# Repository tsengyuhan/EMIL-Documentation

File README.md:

# EMIL-Documentation
The documentation of developing hardware design and wearable solutions.

test

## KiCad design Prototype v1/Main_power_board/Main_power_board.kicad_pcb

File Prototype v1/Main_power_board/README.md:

# Note: Main Power Board

### Features

- Input voltage: 6.2v - 20v (1.2v Maximum Dropout Voltage at 800 mA)
- Regulating the input voltage to 5v. 
- A main switch to turn on/off the entire system manually. 
- I2C connection to the master board. 
- An eneble pin to turn on/off the 

### Difference with the previous version

The trace width and via size are reduced because the manufacturer can produce PCBs with the machine and get more detailed and accurate results.

- Ordinary trace width: 0.4mm
- Via diameter: 0.5mm
- Via hole: 0.3mm
- To decrease the signal interference, I tried to separate the traces based on different signal transmissions (e.g. PWM, I2C, analog reading). 

### Pinout

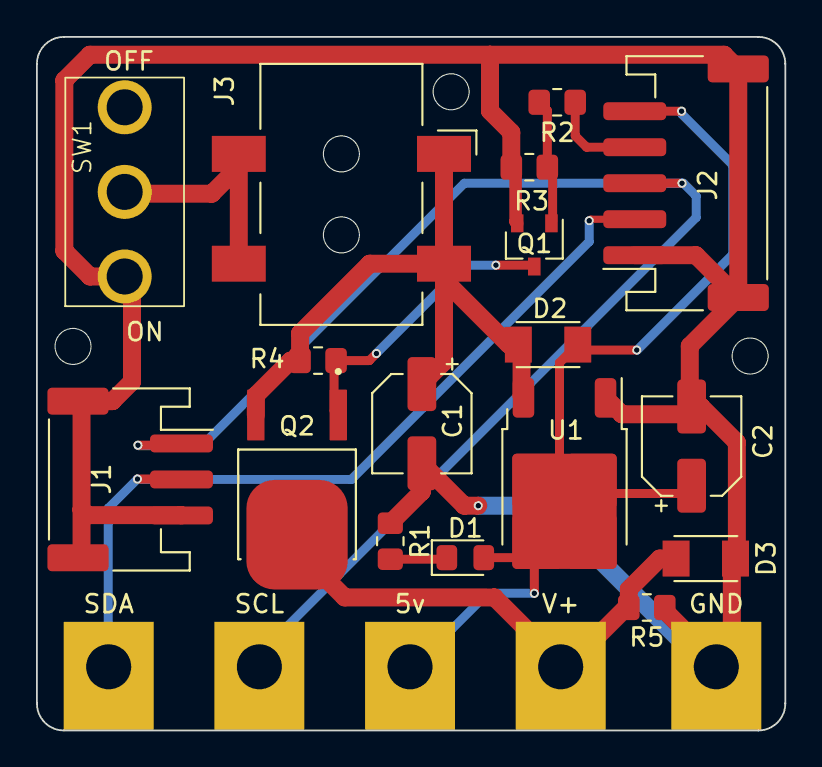
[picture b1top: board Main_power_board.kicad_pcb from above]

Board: 2 copper layers, 41.6 x 38.5 mm, 22 parts (0 on the bottom side), 11 nets.

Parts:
5v: MountingHole_Pad; MountingHole_2.5mm_Pad
C1, C2: 10uF; CP_Elec_5x5.4
D1: LED; LED_0805_2012Metric_Pad1.15x1.40mm_HandSolder
D2, D3: DIODE SCHOT 100V 1A MINISMA; SOD-123T
GND: MountingHole_Pad; MountingHole_2.5mm_Pad
J1: CONN HEADER SMD R/A 3POS 2MM; JST_PH_S3B-PH-SM4-TB_1x03-1MP_P2.00mm_Horizontal
J2: CONN HEADER SMD R/A 5POS 2MM; JST_PH_S5B-PH-SM4-TB_1x05-1MP_P2.00mm_Horizontal
J3: CONN PWR JACK 2X5.5MM; CUIDevices_PJ-002AH-SMT-TR_PWRJack_2x5.5mm
Q1: MOSFET N-CH 30V 1.7A SUPERSOT3; SOT-23-3
Q2: MOSFET P-CH 30V 25A DPAK; TO229P990X238-3N
R1: 499; R_0805_2012Metric_Pad1.20x1.40mm_HandSolder
R2, R3, R4: 10K; R_0805_2012Metric_Pad1.20x1.40mm_HandSolder
R5: 1K; R_0805_2012Metric_Pad1.20x1.40mm_HandSolder
SCL: MountingHole_Pad; MountingHole_2.5mm_Pad
SDA: MountingHole_Pad; MountingHole_2.5mm_Pad
SW1: SWITCH SLIDE SPDT 5A 120VAC; SW_SPDTx03_Slide
U1: IC REG LINEAR 5V 1A DPAK; TO-252-2
V+: MountingHole_Pad; MountingHole_2.5mm_Pad

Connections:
Enable: J2.4, R2.1
unnamed: D1.1 (K), R1.2
unnamed: Q1.3 (D), Q2.1 (G), R4.2
unnamed: Q1.1 (G), R2.2, R3.2
unnamed: J3.2, J3.3, SW1.2 (B)
OUTPUT_PWR: D3.1 (K), Q2.2 (D), R5.2, V+.1
PWR_5V: 5v.1, C2.1, D1.2 (A), D2.2 (A), J2.5, U1.2 (VO)
PWR_12V: C1.1, D2.1 (K), J3.1, Q2.3 (S), R4.1, U1.3 (VI)
PWR_GND: C1.2, C2.2, D3.2 (A), GND.1, J1.3, J2.1, Q1.2 (S), R1.1, R3.1, R5.1, SW1.1 (A), U1.1 (GND)
SCL: J1.1, J2.3, SCL.1
SDA: J1.2, J2.2, SDA.1

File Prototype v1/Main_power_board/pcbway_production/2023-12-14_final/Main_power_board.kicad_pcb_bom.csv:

designator,quantity,value,pack,mpn,mount_type
"C1, C2",2,10uF,CP_Elec_5x5.4,8.65081E+11,smt
D1,1,LED,LED_0805_2012Metric_Pad1.15x1.40mm_HandSolder,LTST-C171GKT,smt
"D2, D3",2,DIODE SCHOT 100V 1A MINISMA,SOD-123T,CDBM1100-G,tht
J1,1,CONN HEADER SMD R/A 3POS 2MM,JST_PH_S3B-PH-SM4-TB_1x03-1MP_P2.00mm_Horizontal,S3B-PH-SM4-TB,smt
J2,1,CONN HEADER SMD R/A 5POS 2MM,JST_PH_S5B-PH-SM4-TB_1x05-1MP_P2.00mm_Horizontal,S5B-PH-SM4-TB,smt
J3,1,CONN PWR JACK 2X5.5MM,CUIDevices_PJ-002AH-SMT-TR_PWRJack_2x5.5mm,PJ-002AH-SMT-TR,smt
Q1,1,MOSFET N-CH 30V 1.7A SUPERSOT3,SOT-23-3,NDS355AN,smt
Q2,1,MOSFET P-CH 30V 25A DPAK,TO229P990X238-3N,NTD25P03LT4G,smt
R1,1,499,R_0805_2012Metric_Pad1.20x1.40mm_HandSolder,RK73H2ATTD4990F,smt
"R2, R3, R4",3,10K,R_0805_2012Metric_Pad1.20x1.40mm_HandSolder,RK73H2ATTD1002F,smt
R5,1,1K,R_0805_2012Metric_Pad1.20x1.40mm_HandSolder,CRCW08051K00FKEAHP,smt
SW1,1,SWITCH SLIDE SPDT 5A 120VAC,SW_SPDTx03_Slide,1103A4CQEA,tht
U1,1,IC REG LINEAR 5V 1A DPAK,TO-252-2,NCV1117DT50RKG,smt

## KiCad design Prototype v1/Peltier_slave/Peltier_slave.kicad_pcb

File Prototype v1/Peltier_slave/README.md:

# Note

### Features

- Input voltage: 4.5v - 44v (with Main Power board: 6v - 20v)
- Control up to two Peltiers to heat up and cool down with pulse width modulation (PWM) signal. 
- Connect with up to four 10K thermistors. 
- Unified Program and Debug Interface (UPDI) pins for programming the board. 
- I2C connection with the master board. 

### Difference with the previous version

The trace width and via size are reduced because the manufacturer can produce PCBs with the machine and get more detailed and accurate results.

- Ordinary trace width: 0.4mm
- Via diameter: 0.5mm
- Via hole: 0.3mm
- To decrease the signal interference, I tried to separate the traces based on different signal transmissions (e.g. PWM, I2C, analog reading). 

### Pinout

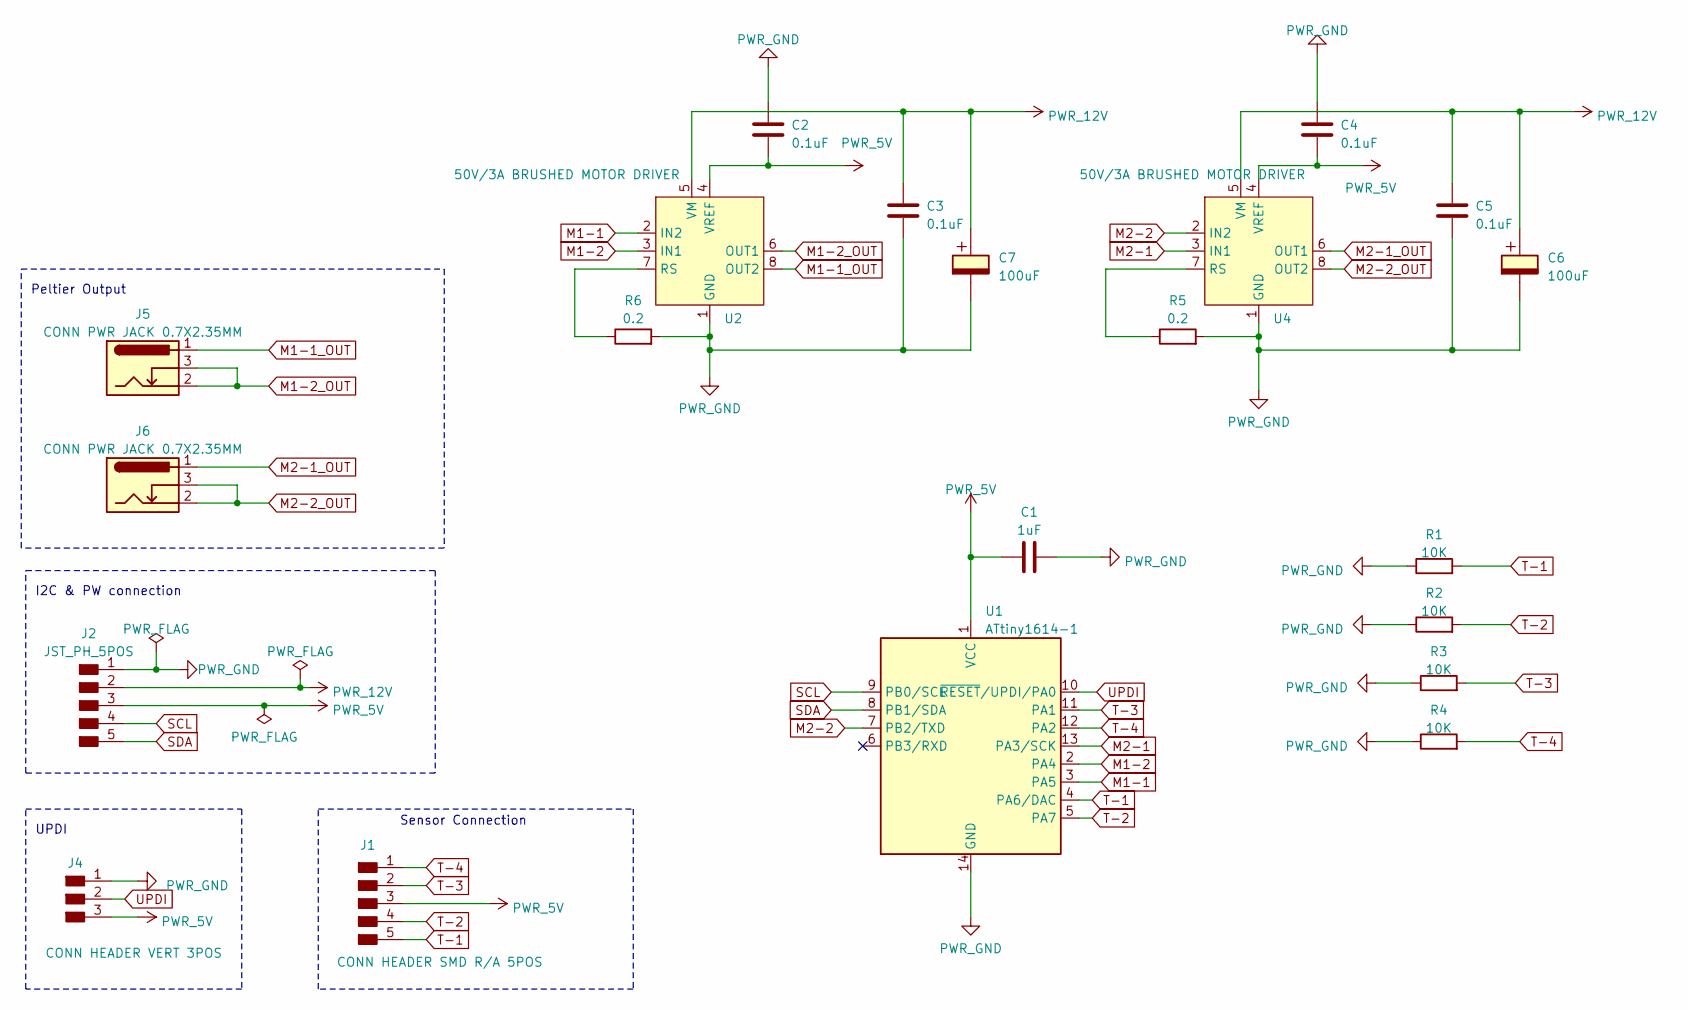
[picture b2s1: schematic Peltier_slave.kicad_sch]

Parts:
C1: 1uF; C_0805_2012Metric_Pad1.18x1.45mm_HandSolder; Mpn C0805C105J3REC7800
C2, C3, C4, C5: 0.1uF; C_0805_2012Metric_Pad1.18x1.45mm_HandSolder; Mpn KGM21NR71H104JT
C6, C7: 100uF; CP_Elec_D6.3mm_H6.1mm; Mpn 35TPV100M6.3X6.1
J1: CONN HEADER SMD R/A 5POS; PinHeader_1x05_P2.54mm_Horizontal_SMD; Mpn TSM-105-02-T-SH-P-TR
J2: JST_PH_5POS; JST_PH_S5B-PH-SM4-TB_1x05-1MP_P2.00mm_Horizontal; Mpn S5B-PH-SM4-TB; LCSC Part # C265104
J4: CONN HEADER VERT 3POS; PinHeader_1x03_P2.54mm_Vertical_THT_D1.4mm; Mpn 61300311121
J5, J6: CONN PWR JACK 0.7X2.35MM; CUIDevices_PJ1-023-SMT-TR_PWRJack_0.7x2.35mm; Mpn PJ1-023-SMT-TR
R1, R2, R3, R4: 10K; R_0805_2012Metric_Pad1.20x1.40mm_HandSolder; Mpn RK73H2ATTD1002F
R5, R6: 0.2; R_0805_2012Metric_Pad1.20x1.40mm_HandSolder; Mpn D1WEL0805CR200F-T5
U1: ATtiny1614-1; SOIC-14_3.9x8.7mm_P1.27mm; Mpn ATTINY1614-SSNR
U2, U4: 50V/3A BRUSHED MOTOR DRIVER; HSOP-8; Mpn TB67H451FNGEL

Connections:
M1-1: U1.3 (PA5), U2.2 (IN2)
M1-1_OUT: J5.1, U2.8 (OUT2)
M1-2: U1.2 (PA4), U2.3 (IN1)
M1-2_OUT: J5.2, J5.3, U2.6 (OUT1)
M2-1: U1.13 (PA3/SCK), U4.3 (IN1)
M2-1_OUT: J6.1, U4.6 (OUT1)
M2-2: U1.7 (PB2/TXD), U4.2 (IN2)
M2-2_OUT: J6.2, J6.3, U4.8 (OUT2)
unnamed: R6.1, U2.7 (RS)
unnamed: R5.1, U4.7 (RS)
PWR_5V: C1.1, C2.2, C4.2, J1.3, J2.3, J4.3, U1.1 (VCC), U2.4 (VREF), U4.4 (VREF)
PWR_12V: C3.1, C5.1, C6.1, C7.1, J2.2, U2.5 (VM), U4.5 (VM)
PWR_GND: C1.2, C2.1, C3.2, C4.1, C5.2, C6.2, C7.2, J2.1, J4.1, R1.1, R2.1, R3.1, R4.1, R5.2, R6.2, U1.14 (GND), U2.1 (GND), U4.1 (GND)
SCL: J2.4, U1.9 (PB0/SCL)
SDA: J2.5, U1.8 (PB1/SDA)
T-1: J1.5, R1.2, U1.4 (PA6/DAC)
T-2: J1.4, R2.2, U1.5 (PA7)
T-3: J1.2, R3.2, U1.11 (PA1)
T-4: J1.1, R4.2, U1.12 (PA2)
UPDI: J4.2, U1.10 (~RESET/UPDI/PA0)

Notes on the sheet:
Peltier Output
Sensor Connection
I2C & PW connection
UPDI

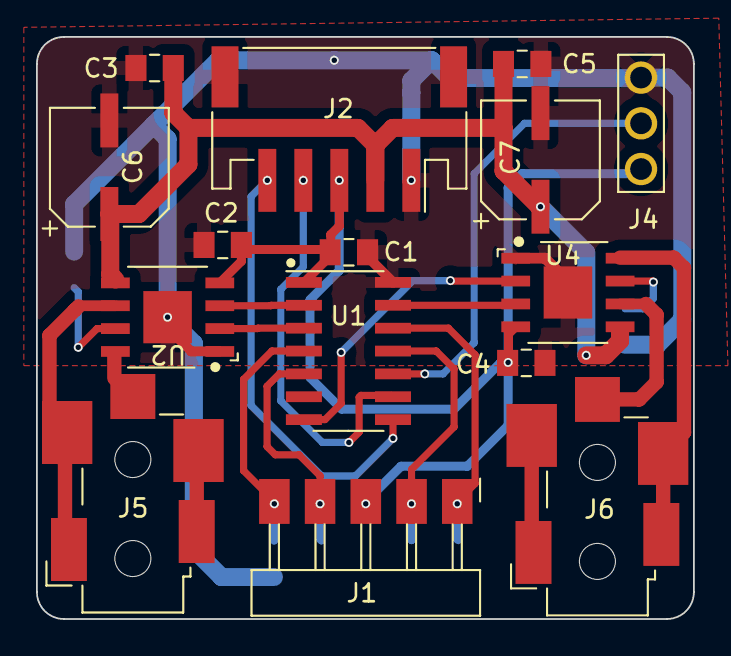
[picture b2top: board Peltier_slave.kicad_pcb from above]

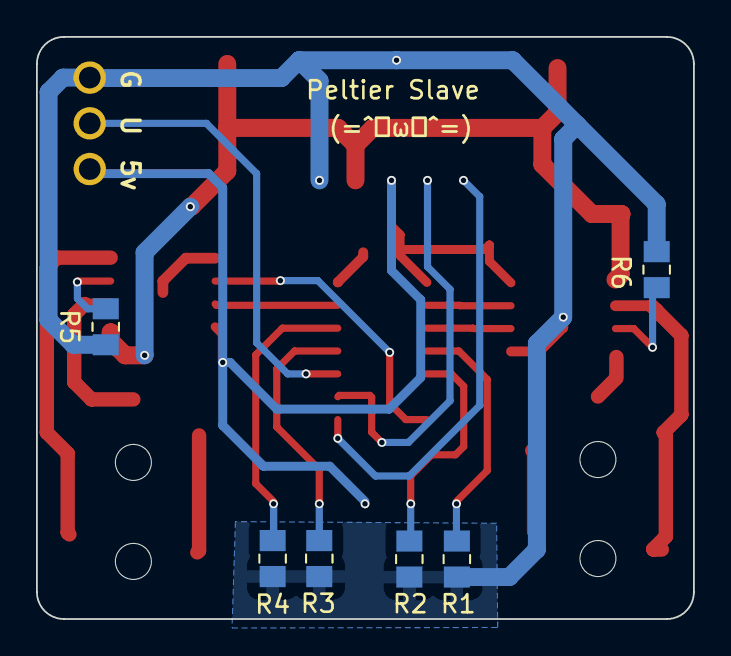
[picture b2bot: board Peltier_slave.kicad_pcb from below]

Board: 2 copper layers, 36.5 x 32.3 mm, 21 parts (6 on the bottom side), 20 nets.

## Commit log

2024-01-09 test multiple read me files
2024-01-16 update Formal prototype v1
2024-01-16 test internal link to another folder
2024-01-16 update Prototype v1
2024-01-16 picture test
2024-01-16 update Prototype v1 peltier slave
2024-01-16 markdown pic size test
2024-01-16 prototype v1 peltier slave update
2024-01-16 add gitignore file
2024-01-16 prototype v1 update
2024-01-16 move .gitignore
